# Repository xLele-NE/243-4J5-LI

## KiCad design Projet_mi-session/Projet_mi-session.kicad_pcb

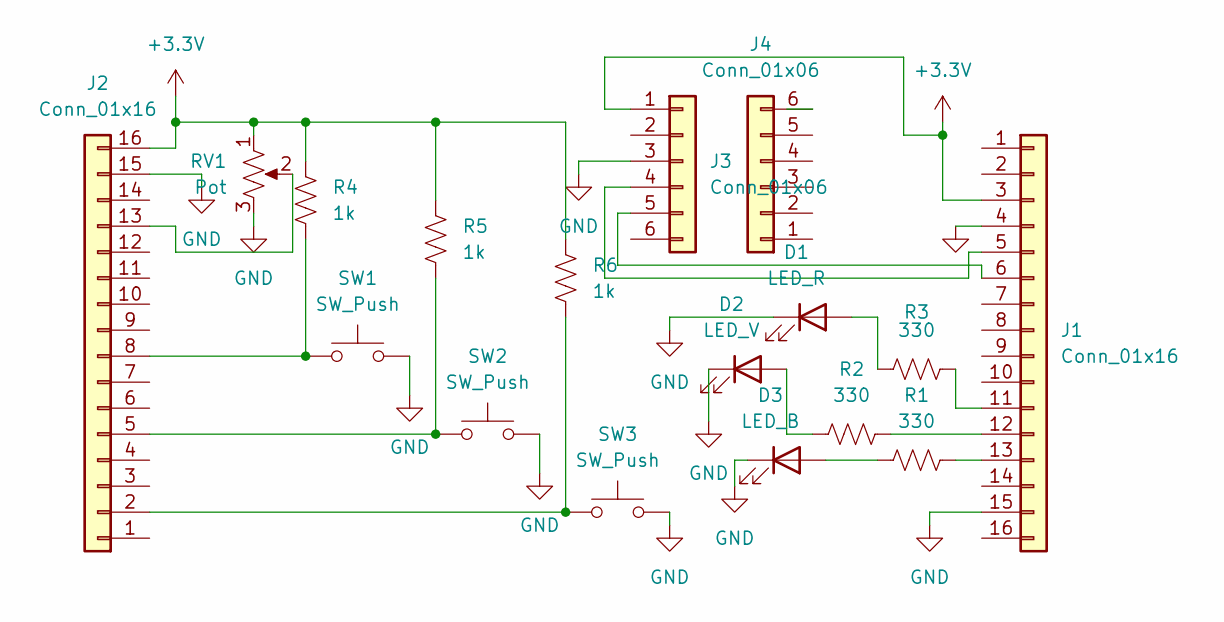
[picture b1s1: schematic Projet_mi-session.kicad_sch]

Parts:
D1: LED_R; LED_D5.0mm_Clear
D2: LED_V; LED_D5.0mm_Clear
D3: LED_B; LED_D5.0mm_Clear
J1, J2: Conn_01x16; PinHeader_1x16_P2.54mm_Vertical
J3, J4: Conn_01x06; PinHeader_1x06_P2.54mm_Vertical
R1, R2, R3: 330; R_Axial_DIN0207_L6.3mm_D2.5mm_P7.62mm_Horizontal
R4, R5, R6: 1k; R_Axial_DIN0207_L6.3mm_D2.5mm_P7.62mm_Horizontal
RV1: Pot; Potentiometer_Bourns_3386P_Vertical
SW1, SW2, SW3: SW_Push; SW_B3WN-6002

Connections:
+3.3V: J1.3, J2.16, J3.1, R4.1, R5.1, R6.1, RV1.1
GND: D1.1 (K), D2.1 (K), D3.1 (K), J1.4, J1.15, J2.15, J3.3, RV1.3, SW1.2, SW2.2, SW3.2
unnamed: D1.2 (A), R3.1
unnamed: D2.2 (A), R2.1
unnamed: D3.2 (A), R1.1
unnamed: J1.5, J3.4
unnamed: J1.6, J3.5
unnamed: J1.11, R3.2
unnamed: J1.12, R2.2
unnamed: J1.13, R1.2
unnamed: J2.2, R6.2, SW3.1
unnamed: J2.5, R5.2, SW2.1
unnamed: J2.8, R4.2, SW1.1
unnamed: J2.13, RV1.2

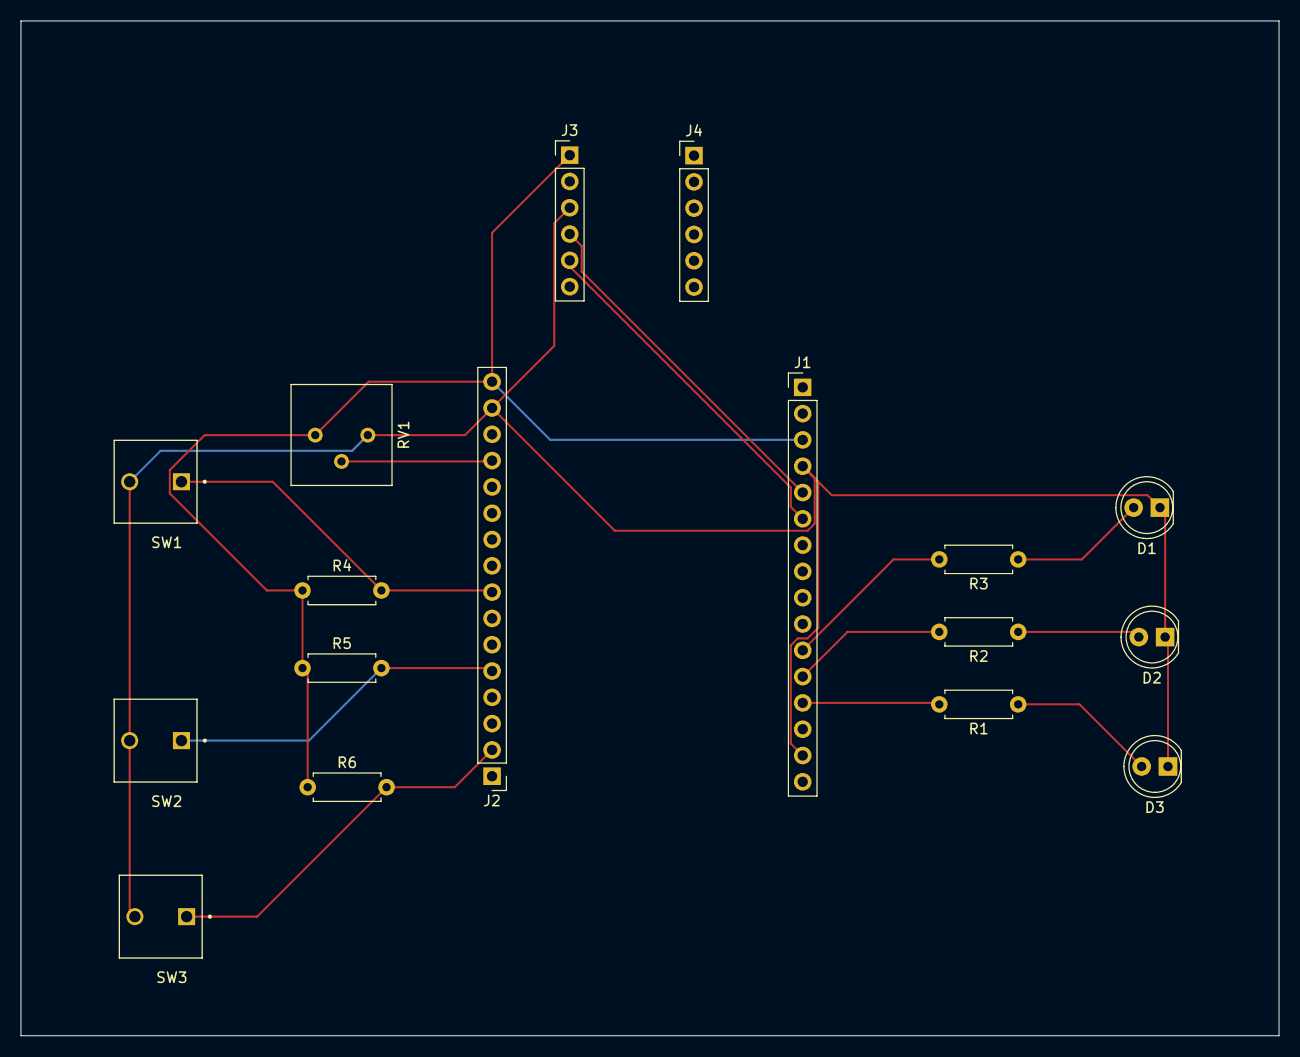
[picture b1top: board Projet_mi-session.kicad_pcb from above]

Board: 2 copper layers, 121.5 x 98.0 mm, 17 parts (0 on the bottom side), 14 nets.

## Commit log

2026-02-26 update: implémentation des boutons physiques et personnalisation de l'UI (fond rose)
2026-03-12 dépo du PCB
2026-03-12 dépo gerbers
2026-03-26 Projet de mi-session : Simon, accéléromètre, potentiomètre, LEDs, boutons
2026-03-26 Ajout README du projet de mi-session : schéma, BOM, topics MQTT, instructions
2026-03-26 photo
2026-03-26 projet
2026-04-23 lora
2026-04-23 Fixed nested repositories by removing internal .git folders
2026-04-23 Ajout code
2026-04-23 regler probleme sous-depot
2026-05-21 kicad
2026-05-21 Programme
2026-05-21 add: interface tactile haute performance via framebuffer direct (mmap)
2026-05-21 allo
